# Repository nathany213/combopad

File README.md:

# combopad
So basically, this is a 3x3 macropad, except it has a unique function: you can enter specific chains of digits to do "secret" functions (preset or customisable), just like entering a cheat code in a game.

## main components used
 - A SW10 Rotary encoder switch
 - An RP2040 Xiao Seed Studio microcontroller
 - 0.91" (i think) OLED Display

# PCB (KiCad)
## Schematics design:

## PCB design:

## CAD (Onshape)
the casing is split into three pieces: 
- the "cushioned" base that has a lowered part for the xiao to go (since my xiao is inconveniently on the bottom half)
- the walls (with a usb hole to plug into the xiao)
- and the cover

## notices:
 - THE combopad.ino CODE IS NOT FINISHED YET. I WILL UPDATE IT ONCE THE MACROPAD ARRIVES.

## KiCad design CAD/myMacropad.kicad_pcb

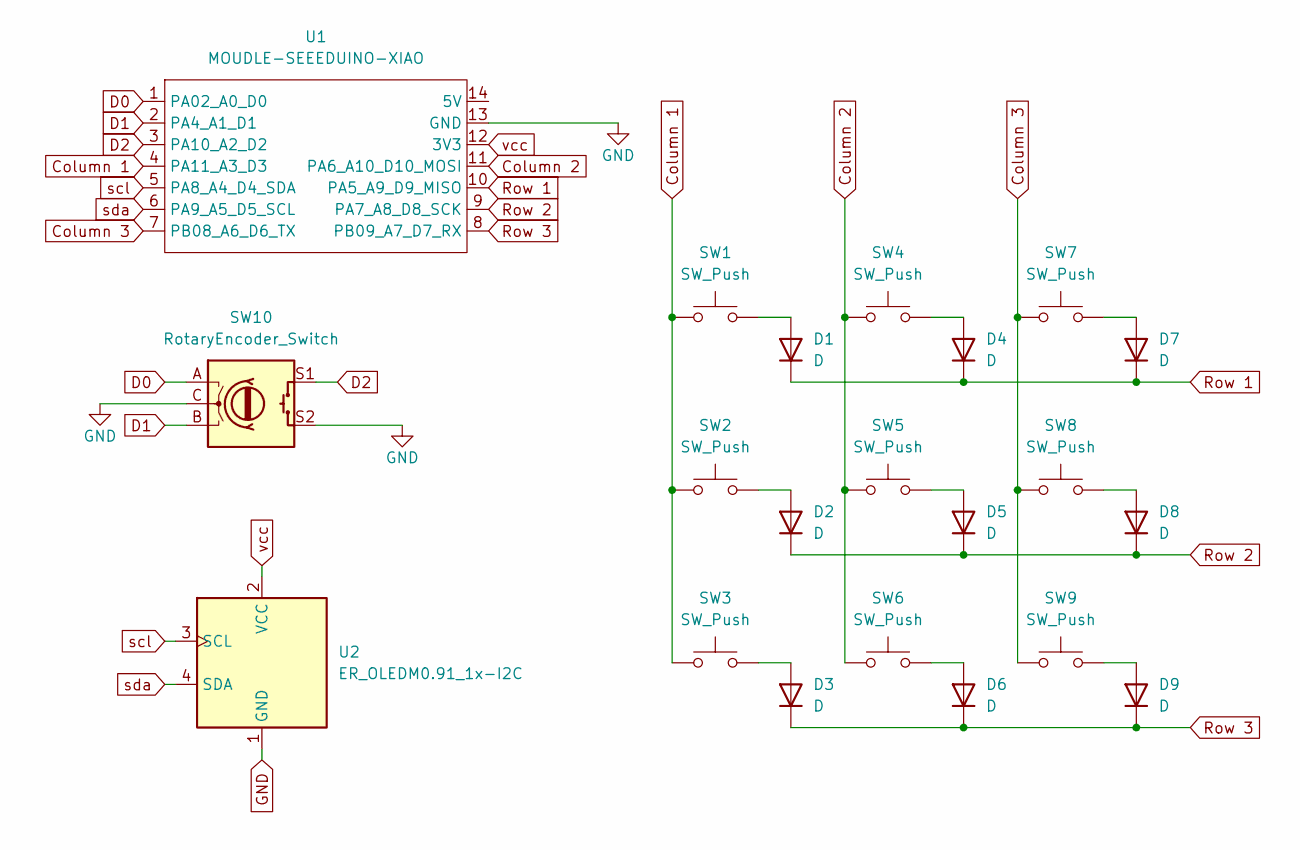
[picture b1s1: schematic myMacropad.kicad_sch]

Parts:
D1, D2, D3, D4, D5, D6, D7, D8, D9: D; D_DO-35_SOD27_P7.62mm_Horizontal
SW1, SW2, SW3, SW4, SW5, SW6, SW7, SW8, SW9: SW_Push; SW_Cherry_MX_1.00u_PCB
SW10: RotaryEncoder_Switch; RotaryEncoder_Alps_EC11E-Switch_Vertical_H20mm_CircularMoun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
U1: MOUDLE-SEEEDUINO-XIAO; XIAO-Generic-Hybrid-14P-2.54-21X17.8MM
U2: ER_OLEDM0.91_1x-I2C

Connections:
Column 1: SW1.1, SW2.1, SW3.1, U1.4 (PA11_A3_D3)
Column 2: SW4.1, SW5.1, SW6.1, U1.11 (PA6_A10_D10_MOSI)
Column 3: SW7.1, SW8.1, SW9.1, U1.7 (PB08_A6_D6_TX)
D0: SW10.A, U1.1 (PA02_A0_D0)
D1: SW10.B, U1.2 (PA4_A1_D1)
D2: SW10.S1, U1.3 (PA10_A2_D2)
GND: SW10.C, SW10.S2, U1.13 (GND), U2.1 (GND)
unnamed: D1.2 (A), SW1.2
unnamed: D2.2 (A), SW2.2
unnamed: D3.2 (A), SW3.2
unnamed: D4.2 (A), SW4.2
unnamed: D5.2 (A), SW5.2
unnamed: D6.2 (A), SW6.2
unnamed: D7.2 (A), SW7.2
unnamed: D8.2 (A), SW8.2
unnamed: D9.2 (A), SW9.2
Row 1: D1.1 (K), D4.1 (K), D7.1 (K), U1.10 (PA5_A9_D9_MISO)
Row 2: D2.1 (K), D5.1 (K), D8.1 (K), U1.9 (PA7_A8_D8_SCK)
Row 3: D3.1 (K), D6.1 (K), D9.1 (K), U1.8 (PB09_A7_D7_RX)
scl: U1.5 (PA8_A4_D4_SDA), U2.3 (SCL)
sda: U1.6 (PA9_A5_D5_SCL), U2.4 (SDA)
vcc: U1.12 (3V3), U2.2 (VCC)

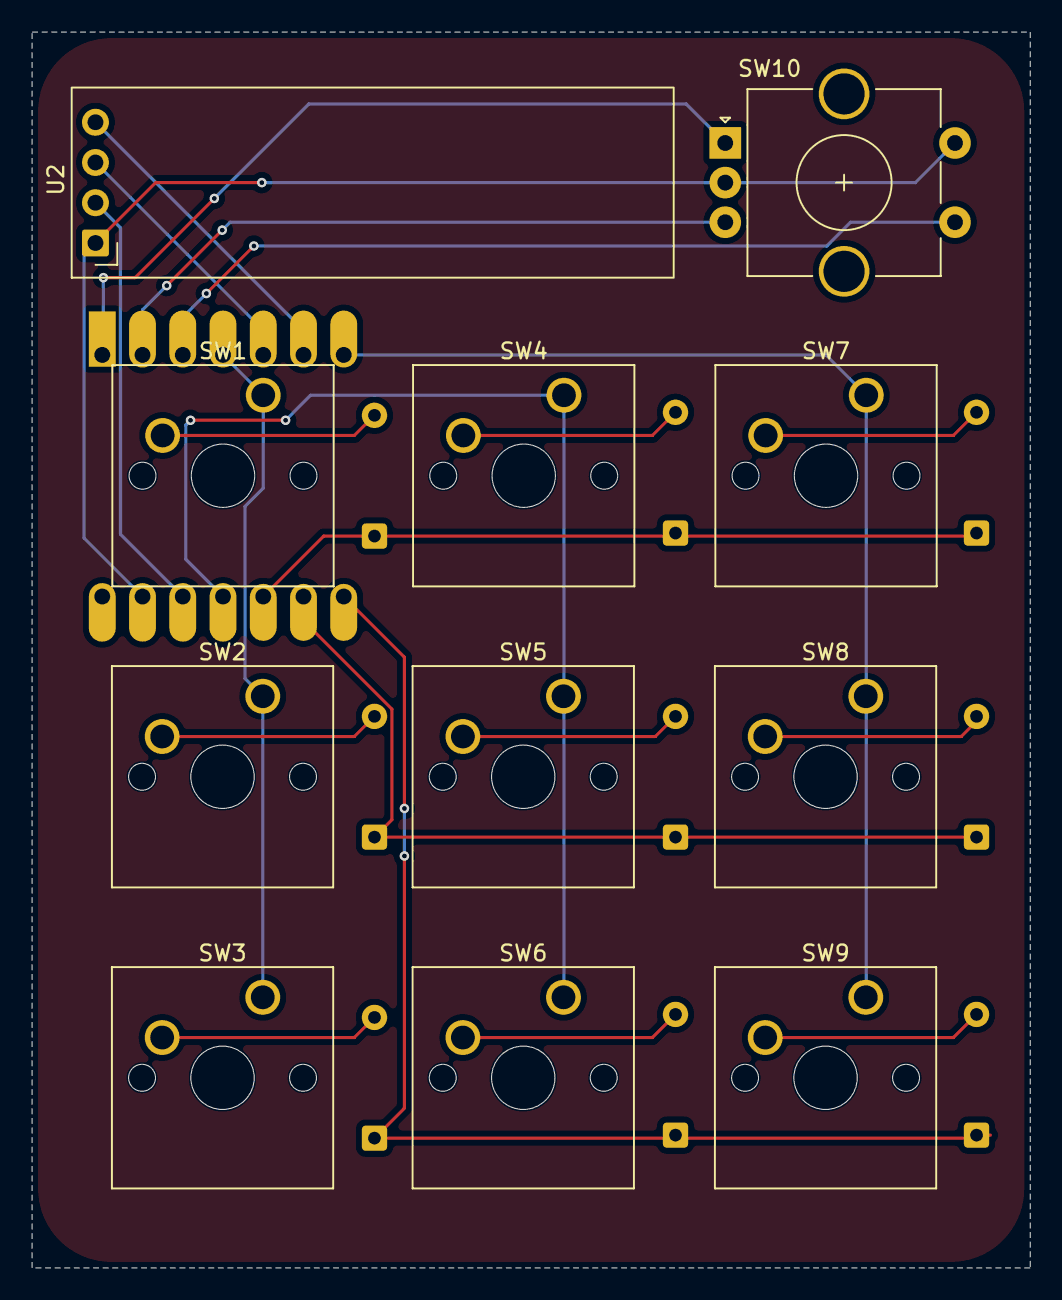
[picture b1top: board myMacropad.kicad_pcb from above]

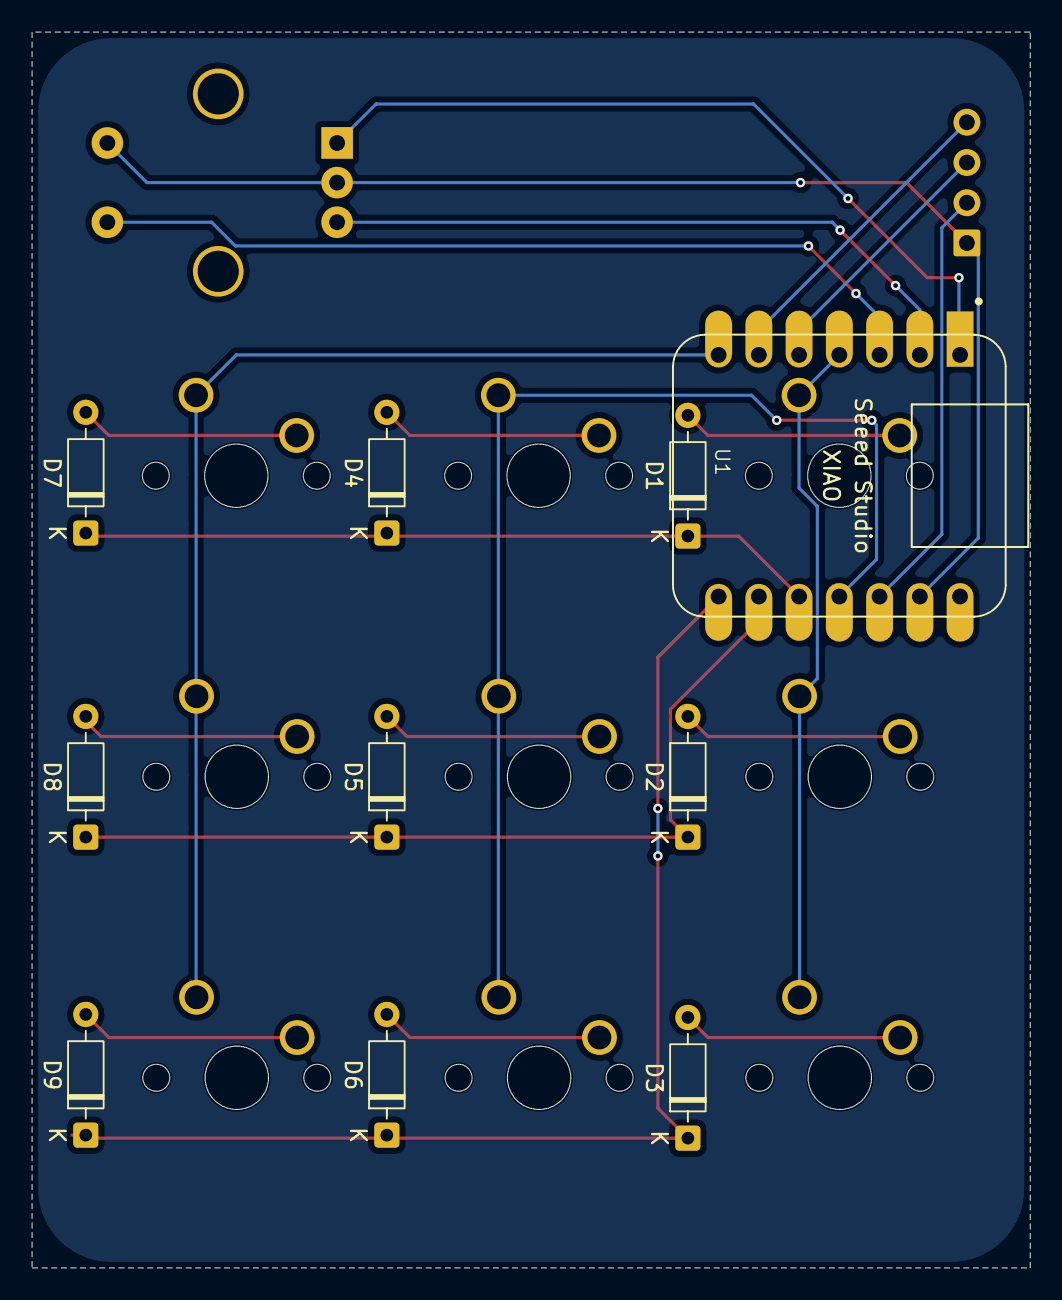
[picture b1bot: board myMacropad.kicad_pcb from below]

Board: 2 copper layers, 63.0 x 78.0 mm, 21 parts (10 on the bottom side), 22 nets.
